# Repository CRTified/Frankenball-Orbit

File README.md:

# Warning: This PCB is untested. It was never fabricated and never tested.

# Frankenball Orbit

This project is a drop-in replacement PCB for the Kensington Orbit.
Besides the basic functionality, it exposes 5 additional GPIO pins and is 
powered by QMK (TODO) on an STM32F411.

The sensor used in the Kensington Orbit is an ADNS-5050.

This project was mostly intended to be a precursor for a different PCB drop-in.

## Rendered PCB

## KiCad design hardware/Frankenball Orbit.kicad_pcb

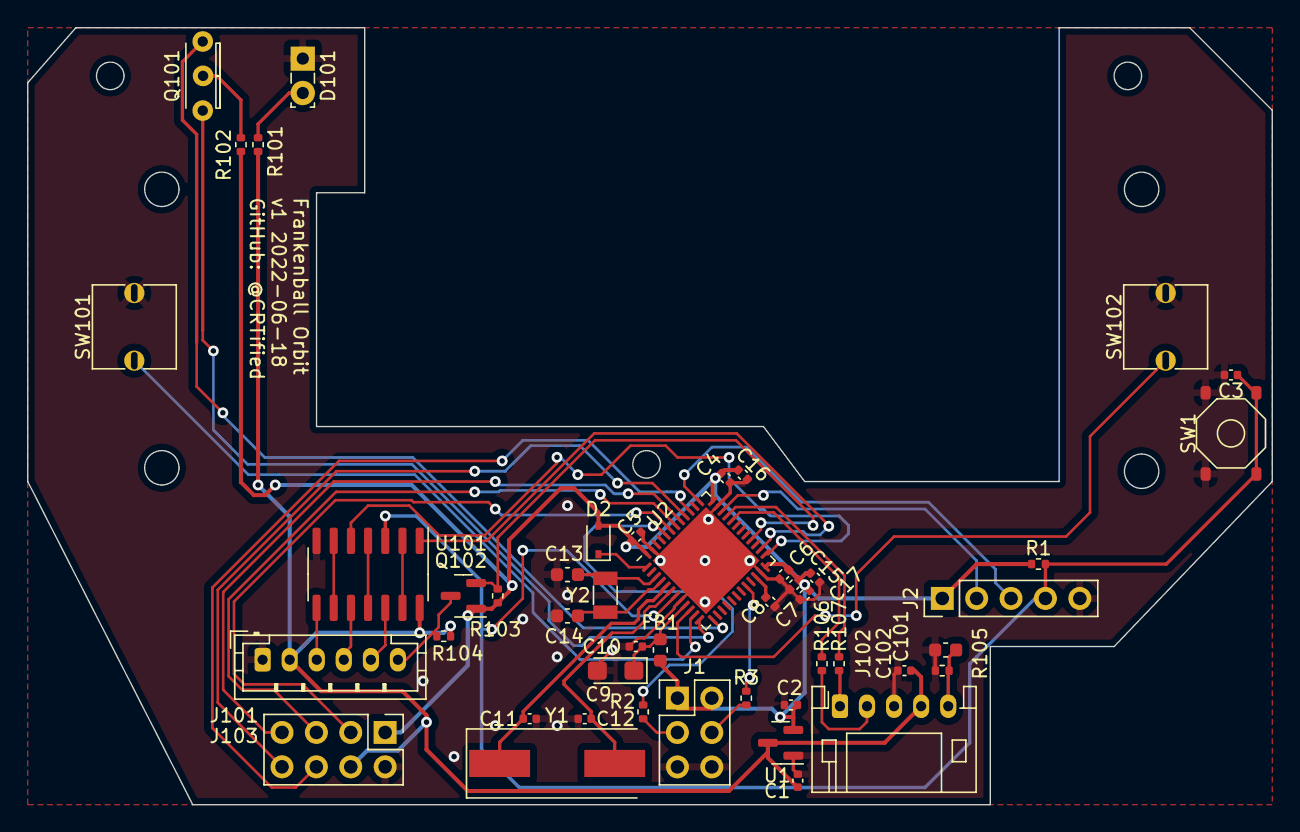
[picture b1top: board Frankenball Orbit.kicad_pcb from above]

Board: 2 copper layers, 91.9 x 57.4 mm, 47 parts (0 on the bottom side), 43 nets.

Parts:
C1, C2: 1µF; C_0402_1005Metric
C3, C4, C5, C6, C7, C10, C15, C16, C102: 100nF; C_0402_1005Metric
C8: 4.7µF; C_0402_1005Metric
C9: 10µF; CP_EIA-3216-10_Kemet-I
C11, C12: 22pF; C_0402_1005Metric
C13, C14: 10pF; C_0603_1608Metric
C17: 4.7uF; C_0402_1005Metric
C101: 4.7nF; C_0603_1608Metric
D2: D_Schottky; D_SOD-323
D101: LED; LED_SideEmitter_Rectangular_W4.5mm_H1.6mm
FB1: 600Ω@100MHz; L_0603_1608Metric
J1: Conn_02x03_Odd_Even; PinHeader_2x03_P2.54mm_Vertical
J2: Connector_Generic:Conn_01x05; PinHeader_1x05_P2.54mm_Vertical
J101: ADNS-5050; JST_PH_B6B-PH-K_1x06_P2.00mm_Vertical
J102: Conn_01x05_Male; JST_PH_S5B-PH-K_1x05_P2.00mm_Horizontal
J103: Conn_02x04_Odd_Even; PinHeader_2x04_P2.54mm_Vertical
Q101: PT2559B
Q102: 2N7002; SOT-23
R1: 22kΩ; R_0402_1005Metric
R2, R3: 10k; R_0402_1005Metric
R101: 270Ω; R_0402_1005Metric
R102: 4.7kΩ; R_0402_1005Metric
R103, R104, R105: 47k; R_0402_1005Metric
R106, R107: 10Ω; R_0402_1005Metric
SW1: SW_Push; TS-1187A-B-A-B
SW101, SW102: SW_Push; Kailh_SW_Mouse
U1: XC6206PxxxMR; SOT-23
U2: STM32F411CCUx; QFN-48-1EP_7x7mm_P0.5mm_EP5.6x5.6mm
U101: 74HC14; SOIC-14_3.9x8.7mm_P1.27mm
Y1: 8MHz; Crystal_SMD_HC49-SD
Y2: 32.768kHz; Crystal_SMD_3215-2Pin_3.2x1.5mm

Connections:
+3V3: C2.1, C4.1, C5.1, C6.1, C7.1, C15.1, C16.1, C17.1, D2.2 (A), FB1.1, J1.1, J1.2, J2.1, J103.1, Q102.1 (G), R1.1, R102.1, R103.1, U1.2 (VO), U2.24 (VDD), U2.36 (VDD), U2.48 (VDD)
/SCLK_{RAW}: J101.5, U101.12
/SDIO_{RAW}: J101.6, Q102.3 (D), R104.2
/STM32F411/BOOT0: R2.1, U2.44 (BOOT0)
/STM32F411/PA0: SW102.2, U2.10 (PA0)
/STM32F411/PA1: SW101.2, U2.11 (PA1)
/STM32F411/PA2: Q101.1 (E_{A}), U2.12 (PA2)
/STM32F411/PA3: Q101.3 (E_{B}), U2.13 (PA3)
/STM32F411/PA11: R106.1, U2.32 (PA11)
/STM32F411/PA12: R107.1, U2.33 (PA12)
/STM32F411/PA13: J2.2, U2.34 (PA13)
/STM32F411/PA14: J2.3, U2.37 (PA14)
/STM32F411/PB2: R3.2, U2.20 (PB2)
/STM32F411/PB3: J103.6, U2.39 (PB3)
/STM32F411/PB4: J103.8, U2.40 (PB4)
/STM32F411/PB5: J103.7, U2.41 (PB5)
/STM32F411/PB6: J103.5, U2.42 (PB6)
/STM32F411/PB7: J103.3, U2.43 (PB7)
/STM32F411/PBu12: U2.25 (PB12), U101.5
/STM32F411/PBu13: U2.26 (PB13), U101.1
/STM32F411/PBu15: Q102.2 (S), R103.2, U2.28 (PB15)
/STM32F411/VBAT_{I}: D2.1 (K), U2.1 (VBAT)
/STM32F411/VREF+: C9.1, C10.1, FB1.2, U2.9 (VDDA)
/STM32F411/XTAL_8M_1: C11.1, U2.5 (PH0), Y1.1
/STM32F411/XTAL_8M_2: C12.1, U2.6 (PH1), Y1.2
/STM32F411/XTAL_32K_1: C13.1, U2.3 (PC14), Y2.1
/STM32F411/XTAL_32K_2: C14.1, U2.4 (PC15), Y2.2
/USB_DM: J102.2, R106.2
/USB_DP: J102.1, R107.2
/USB_SHIELD: C101.1, J102.5, R105.1
/~CS_{RAW}: J101.3, U101.8
/~RST: C3.1, J2.4, R1.2, SW1.2, U2.7 (NRST), U101.3
/~RST_{RAW}: J101.4, U101.10
GND: C1.2, C2.2, C3.2, C4.2, C5.2, C6.2, C7.2, C8.2, C9.2, C10.2, C11.2, C12.2, C13.2, C14.2, C15.2, C16.2, C17.2, C101.2, C102.2, D101.1 (K), J1.5, J1.6, J2.5, J101.1, J102.3, J103.2, R105.2, SW1.1, SW101.1, SW102.1, U1.1 (GND), U2.8 (VSSA), U2.23 (VSS), U2.35 (VSS), U2.47 (VSS), U2.49 (VSS), U101.7 (GND)
unnamed: C8.1, U2.22 (VCAP1)
unnamed: D101.2 (A), R101.2
unnamed: J1.3, R2.2
unnamed: J1.4, R3.1
unnamed: Q101.2 (C), R102.2
unnamed: U101.6, U101.9
unnamed: U101.4, U101.11
unnamed: U101.2, U101.13
VCC: C1.1, C102.1, J101.2, J102.4, J103.4, R101.1, R104.1, U1.3 (VI), U101.14 (VCC)

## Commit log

2022-06-18 Initial content
2022-06-18 Routing finished
2022-06-18 Finalize PCB
2022-06-18 Add README, move files
2022-06-18 Add gitignore
2022-06-18 Fix image
2022-06-18 Added more filtering caps to STM32 supply
